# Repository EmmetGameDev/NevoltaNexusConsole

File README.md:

[See the build and design on YouTube!](https://www.youtube.com/watch?v=XNRuj0vmZO0)

# Nevolta Nexus

The Nexus is a **retro games console** based on the Raspberry Pi Zero 2W and the ESP32-S3. The console features:
- Custom wireless controller
- Active cooling system
- Custom PCBs
- Fully open source design

"Nevolta" is the name for my personal console line-up. **(more are coming soon!)**

# Files

- The "Printables" folder contains labeled 3D printable files for the Console unit as well as the Controller.
- The "PCBs" folder contains GERBER files, as well as KiCad project, schematic, and layout files.
- The "Firmware" folder contains two .INO files for the Console and Controller ESPs, respectively.

# Setup

## ESP32-S3 Microcontrollers
- The ESPs can be programmed when already soldered onto the board, since a data connection is present in the USB-C connector.
- Respective firmware (.INO) files are to be flashed via the [Arduino IDE](https://www.arduino.cc/en/software/)

## Raspberry Pi Zero 2W
- A generic RetroPie build is used for the Pi, which is included in the [Raspberry Pi Imager](https://www.raspberrypi.com/software/)
- Software [GPIOnext](https://github.com/mholgatem/GPIOnext) is used for GPIO button usage according to the instructions provided on the repo.
- [This tutorial](https://www.youtube.com/watch?v=BV_nVu8Be7M) is a good reference for the setup of the software.

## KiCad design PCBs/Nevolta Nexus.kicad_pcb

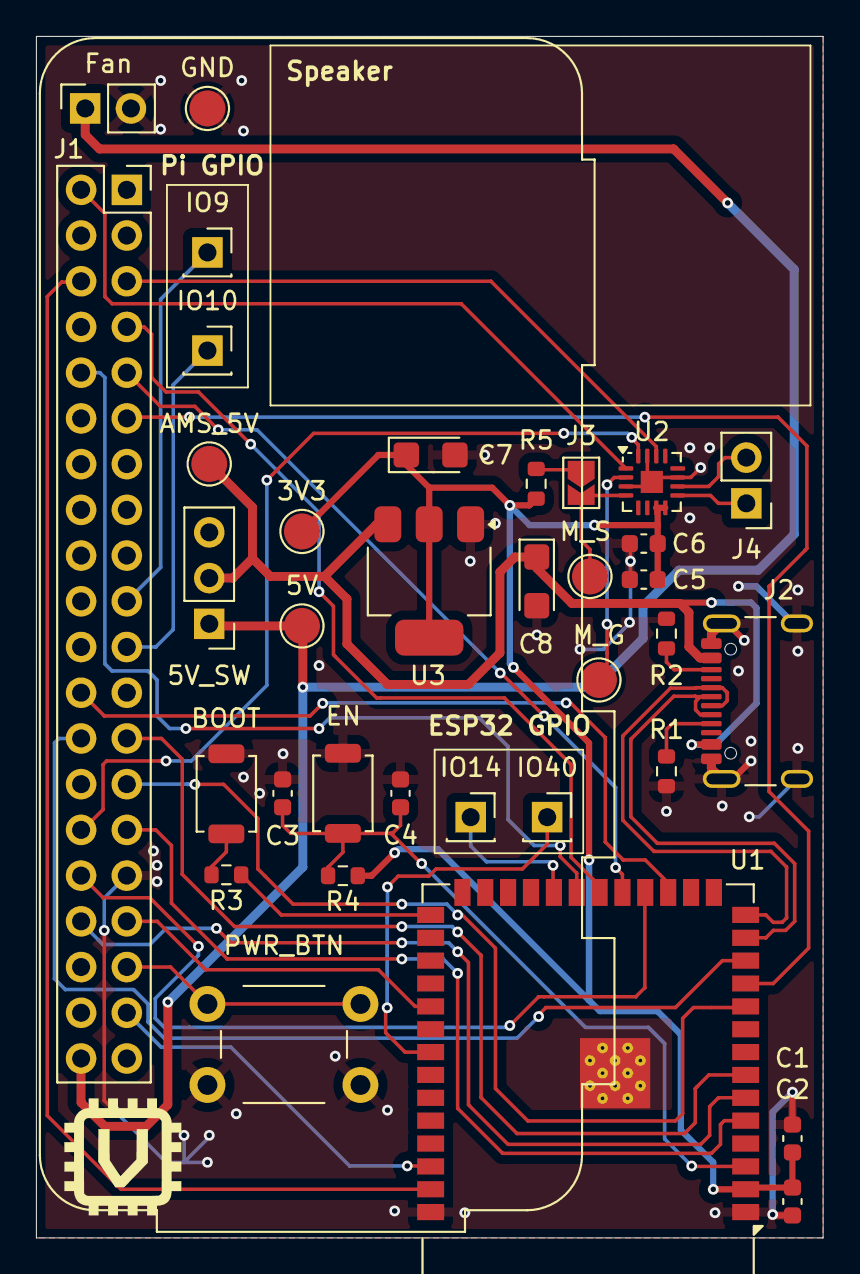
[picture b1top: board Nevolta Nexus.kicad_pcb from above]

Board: 2 copper layers, 43.7 x 66.8 mm, 35 parts (0 on the bottom side), 38 nets.

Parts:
3V3: 3v3; TestPoint_Pad_D2.0mm
5V: 5V; TestPoint_Pad_D2.0mm
5V_SW: Vbus_SW; PinHeader_1x03_P2.54mm_Vertical
AMS_5V: AMS_5V; TestPoint_Pad_D2.0mm
BOOT: BOOT; SW_SPST_TS-1088-xR020
C1: 22uF; C_0603_1608Metric
C2, C4, C6: 100nF; C_0603_1608Metric
C3, C5: 10uF; C_0603_1608Metric
C7: 22uF; CP_EIA-3216-18_Kemet-A
C8: 10uF; CP_EIA-3216-18_Kemet-A
EN: EN; SW_SPST_TS-1088-xR020
Fan: Fan_Conn; PinSocket_1x02_P2.54mm_Vertical
GND: GND; TestPoint_Pad_D2.0mm
IO9: Pi_IO9; PinSocket_1x01_P2.54mm_Vertical
IO10: Pi_IO10; PinSocket_1x01_P2.54mm_Vertical
IO14: GPIO14; PinSocket_1x01_P2.54mm_Vertical
IO40: GPIO40; PinSocket_1x01_P2.54mm_Vertical
J1: Pi Zero 2W; Raspberry Pi Zero 2 W - Clear
J2: USB_C_Receptacle_USB2.0_16P; USB_C_Receptacle_GCT_USB4105-xx-A_16P_TopMnt_Horizontal
J3: SolderJumper-2_P1.3mm_Open_TrianglePad1.0x1.5mm
J4: SpeakerConn; PinHeader_1x02_P2.54mm_Vertical
M_G: MAX_GAIN; TestPoint_Pad_D2.0mm
M_S: MAX_SD; TestPoint_Pad_D2.0mm
PWR_BTN: PWR; SW_PUSH_8mm_H5mm_custom
R1, R2: 5.1k; R_0603_1608Metric
R3: 100R; R_0603_1608Metric
R4: 10k; R_0603_1608Metric
R5: 1M; R_0603_1608Metric
U1: ESP32-S3-WROOM-1
U2: MAX98357A; TQFN-16-1EP_3x3mm_P0.5mm_EP1.23x1.23mm
U3: AMS1117-3.3; SOT-223-3_TabPin2

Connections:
+3V3: 3V3.1, C1.1, C2.1, C5.2, C6.2, C7.1, R4.1, R5.1, U1.2 (3V3), U2.7 (VDD), U2.8 (VDD), U3.2 (VO)
+5V: 5V.1, 5V_SW.1 (A), Fan.1, J1.40
AMS_5V: 5V_SW.2 (B), AMS_5V.1, C8.1, J2.A4 (VBUS), J2.A9 (VBUS), J2.B4 (VBUS), J2.B9 (VBUS), U3.3 (VI)
BOOT: R3.1, U1.27 (IO0)
BTN_A: J1.37, U1.38 (IO2)
BTN_B: J1.34, U1.6 (IO6)
BTN_DOWN: J1.9, U1.19 (IO11)
BTN_L: J1.32, U1.18 (IO10)
BTN_LEFT: J1.7, U1.20 (IO12)
BTN_R: J1.6, U1.39 (IO1)
BTN_RIGHT: J1.10, U1.21 (IO13)
BTN_SELECT: J1.25, U1.7 (IO7)
BTN_START: J1.27, U1.10 (IO17)
BTN_UP: J1.11, U1.11 (IO18)
BTN_VOLD: J1.26, U1.12 (IO8)
BTN_VOLU: J1.24, U1.17 (IO9)
BTN_X: J1.33, U1.31 (IO38)
BTN_Y: J1.29, U1.5 (IO5)
Data+: J2.A6 (D+), J2.B6 (D+), U1.14 (USB_D+)
Data-: J2.A7 (D-), J2.B7 (D-), U1.13 (USB_D-)
EN: C3.1, C4.1, EN.1, R4.2, U1.3 (EN)
GND: BOOT.2, C1.2, C2.2, C3.2, C4.2, C5.1, C6.1, C7.2, C8.2, EN.2, Fan.2, GND.1, J1.31, J2.A1 (GND), J2.A12 (GND), J2.B1 (GND), J2.B12 (GND), J2.S1 (SHIELD), PWR_BTN.2, R1.2, R2.1, U1.1 (GND), U1.40 (GND), U1.41 (GND), U2.3 (GND), U2.11 (GND), U2.15 (GND), U2.17 (PAD), U3.1 (GND)
GPIO14: IO14.1, U1.22 (IO14)
GPIO40: IO40.1, U1.33 (IO40)
I2S_BCLK: J1.30, U2.16 (BCLK)
I2S_DIN: J1.2, U2.1 (DIN)
I2S_LRC: J1.5, U2.14 (LRCLK)
MAX_GAIN: M_G.1, U2.2 (GAIN_SLOT)
MAX_SD: J3.2, M_S.1, U2.4 (~SD_MODE)
unnamed: J2.A5 (CC1), R1.1
unnamed: J2.B5 (CC2), R2.2
unnamed: J3.1, R5.2
unnamed: J4.1, U2.9 (OUTP)
unnamed: J4.2, U2.10 (OUTN)
unnamed: BOOT.1, R3.2
POWER_BTN: J1.35, PWR_BTN.1
Pi_GPIO9: IO9.1, J1.19
Pi_GPIO10: IO10.1, J1.21

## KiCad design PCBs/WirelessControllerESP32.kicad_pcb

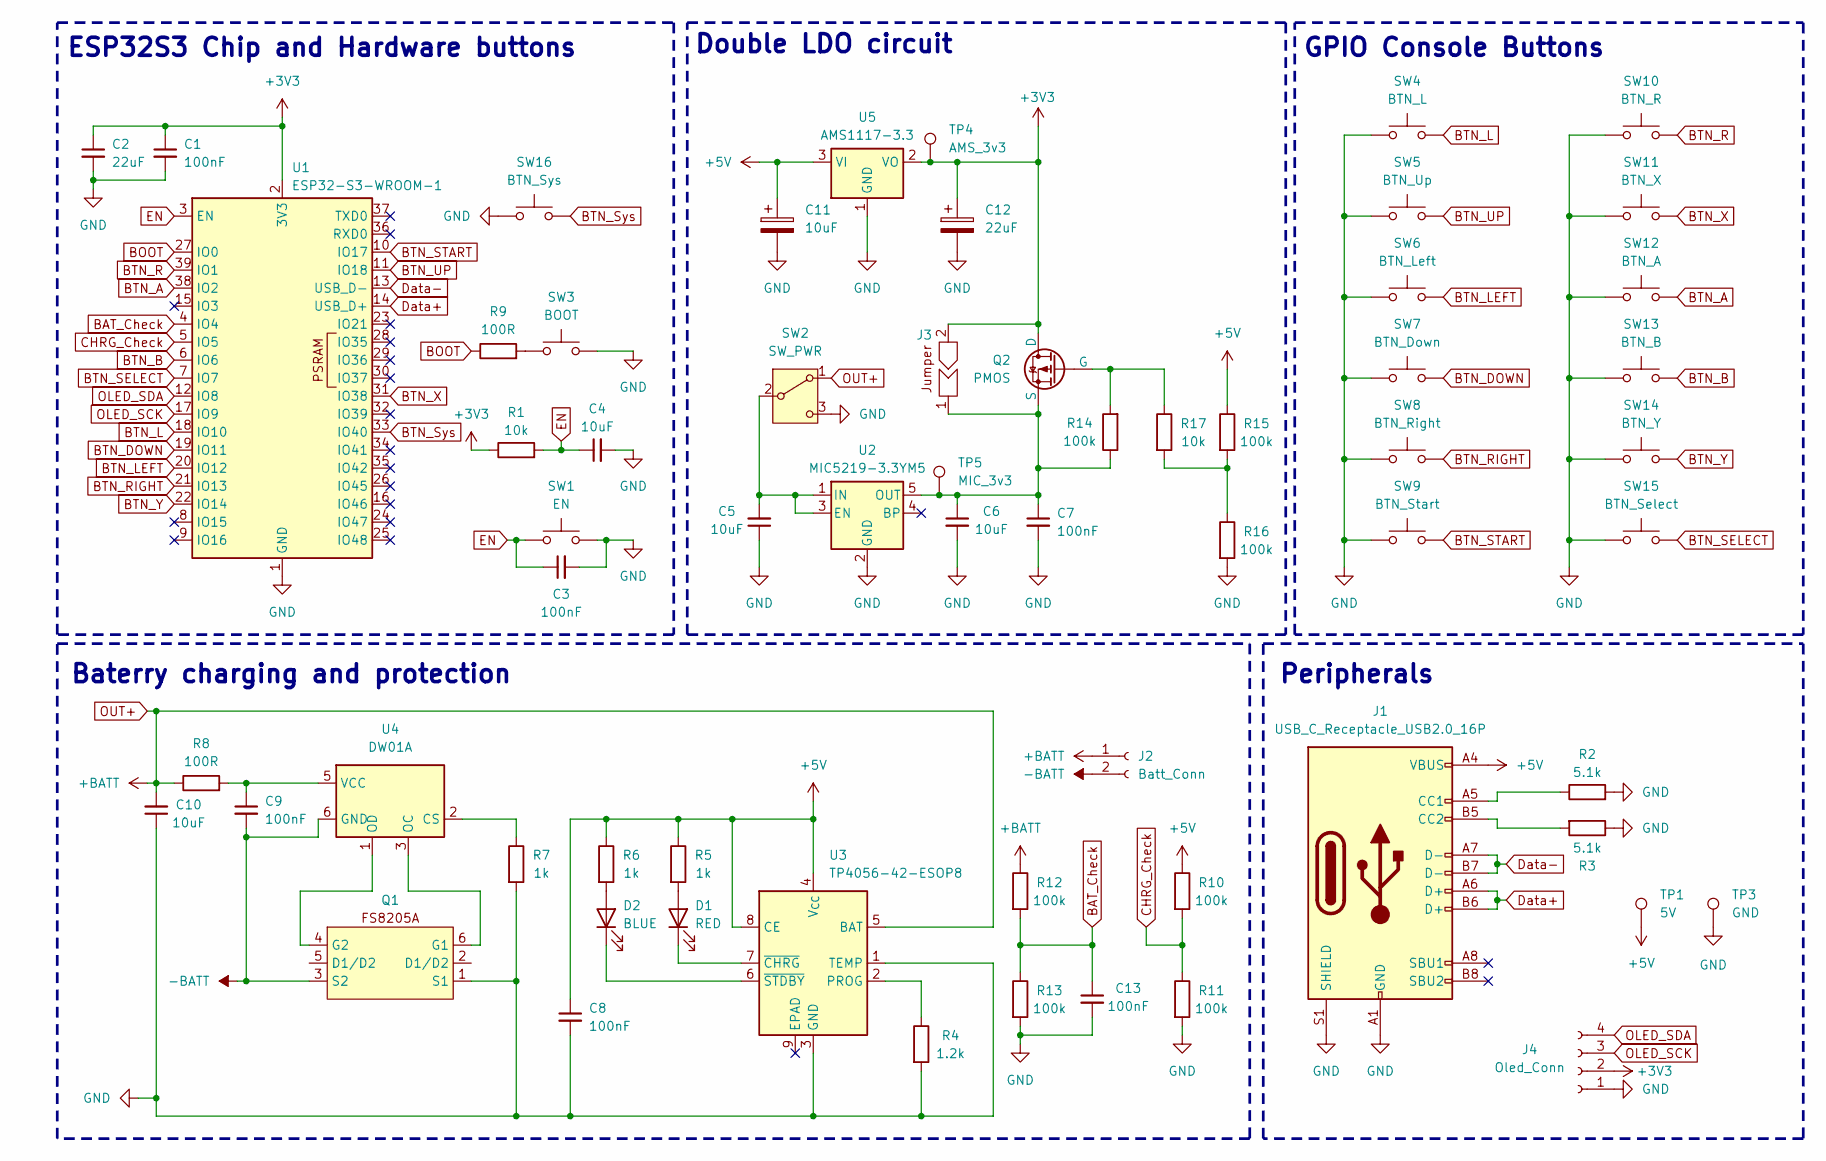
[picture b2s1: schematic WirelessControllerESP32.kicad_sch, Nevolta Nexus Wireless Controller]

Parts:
C1, C3, C7, C8, C9, C13: 100nF; C_0603_1608Metric
C2: 22uF; C_0603_1608Metric
C4, C5, C6, C10: 10uF; C_0603_1608Metric
C11: 10uF; CP_EIA-3216-18_Kemet-A
C12: 22uF; CP_EIA-3216-18_Kemet-A
D1: RED; LED_0603_1608Metric
D2: BLUE; LED_0603_1608Metric
J1: USB_C_Receptacle_USB2.0_16P; USB_C_Receptacle_GCT_USB4105-xx-A_16P_TopMnt_Horizontal
J2: Batt_Conn; JST_ZH_S2B-ZR-SM4A-TF_1x02-1MP_P1.50mm_Horizontal
J3: R_0603_1608Metric
J4: Oled_Conn; OLED128x32_1x04_P2.54mm_socket
Q1: SOT-23-6L_TCP
Q2: PMOS; SOT-23
R1, R17: 10k; R_0603_1608Metric
R2, R3: 5.1k; R_0603_1608Metric
R4: 1.2k; R_0603_1608Metric
R5, R6, R7: 1k; R_0603_1608Metric
R8, R9: 100R; R_0603_1608Metric
R10, R11, R12, R13, R14, R15, R16: 100k; R_0603_1608Metric
SW1: EN; SW_SPST_TS-1088-xR020
SW2: SW_PWR; PinSocket_1x03_P2.54mm_Vertical
SW3: BOOT; SW_SPST_TS-1088-xR020
SW4: BTN_L; TS-1224VW
SW5: BTN_Up; SW_PUSH_8mm_H5mm_custom
SW6: BTN_Left; SW_PUSH_8mm_H5mm_custom
SW7: BTN_Down; SW_PUSH_8mm_H5mm_custom
SW8: BTN_Right; SW_PUSH_8mm_H5mm_custom
SW9: BTN_Start; SW_PUSH_8mm_H5mm_custom
SW10: BTN_R; TS-1224VW
SW11: BTN_X; SW_PUSH_8mm_H5mm_custom
SW12: BTN_A; SW_PUSH_8mm_H5mm_custom
SW13: BTN_B; SW_PUSH_8mm_H5mm_custom
SW14: BTN_Y; SW_PUSH_8mm_H5mm_custom
SW15: BTN_Select; SW_PUSH_8mm_H5mm_custom
SW16: BTN_Sys; SW_PUSH_8mm_H5mm_custom
TP1: 5V; TestPoint_Pad_D2.0mm
TP3: GND; TestPoint_Pad_D2.0mm
TP4: AMS_3v3; TestPoint_Pad_D2.0mm
TP5: MIC_3v3; TestPoint_Pad_D2.0mm
U1: ESP32-S3-WROOM-1
U2: MIC5219-3.3YM5; SOT-23-5
U3: TP4056-42-ESOP8; SOIC-8-1EP_3.9x4.9mm_P1.27mm_EP2.41x3.3mm_ThermalVias
U4: DW01A; SOT-23-6
U5: AMS1117-3.3; SOT-223-3_TabPin2

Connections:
+3V3: C1.1, C2.1, C12.1, J3.2, J4.2, Q2.1 (D), R1.1, TP4.1, U1.2 (3V3), U5.2 (VO)
+5V: C8.1, C11.1, J1.A4 (VBUS), J1.A9 (VBUS), J1.B4 (VBUS), J1.B9 (VBUS), R5.1, R6.1, R10.1, R15.1, TP1.1, U3.4 (V_{CC}), U3.8 (CE), U5.3 (VI)
-BATT: C9.2, J2.2, Q1.3 (S2), U4.6 (GND)
BAT_Check: C13.1, R12.2, R13.1, U1.4 (IO4)
BOOT: R9.1, U1.27 (IO0)
BTN_A: SW12.2, U1.38 (IO2)
BTN_B: SW13.2, U1.6 (IO6)
BTN_DOWN: SW7.2, U1.19 (IO11)
BTN_L: SW4.2, U1.18 (IO10)
BTN_LEFT: SW6.2, U1.20 (IO12)
BTN_R: SW10.2, U1.39 (IO1)
BTN_RIGHT: SW8.2, U1.21 (IO13)
BTN_SELECT: SW15.2, U1.7 (IO7)
BTN_START: SW9.2, U1.10 (IO17)
BTN_Sys: SW16.2, U1.33 (IO40)
BTN_UP: SW5.2, U1.11 (IO18)
BTN_X: SW11.2, U1.31 (IO38)
BTN_Y: SW14.2, U1.22 (IO14)
CHRG_Check: R10.2, R11.1, U1.5 (IO5)
Data+: J1.A6 (D+), J1.B6 (D+), U1.14 (USB_D+)
Data-: J1.A7 (D-), J1.B7 (D-), U1.13 (USB_D-)
EN: C3.1, C4.1, R1.2, SW1.1, U1.3 (EN)
GND: C1.2, C2.2, C3.2, C4.2, C5.1, C6.2, C7.2, C8.2, C10.1, C11.2, C12.2, C13.2, J1.A1 (GND), J1.A12 (GND), J1.B1 (GND), J1.B12 (GND), J1.S1 (SHIELD), J4.1, Q1.1 (S1), R2.2, R3.1, R4.2, R7.2, R11.2, R13.2, R16.2, SW1.2, SW2.3 (C), SW3.2, SW4.1, SW5.1, SW6.1, SW7.1, SW8.1, SW9.1, SW10.1, SW11.1, SW12.1, SW13.1, SW14.1, SW15.1, SW16.1, TP3.1, U1.1 (GND), U1.40 (GND), U1.41 (GND), U2.2 (GND), U3.1 (TEMP), U3.3 (GND), U5.1 (GND)
unnamed: D1.2 (A), R5.2
unnamed: D1.1 (K), U3.7 (~CHRG)
unnamed: D2.2 (A), R6.2
unnamed: D2.1 (K), U3.6 (~STDBY)
unnamed: J1.A5 (CC1), R2.1
unnamed: J1.B5 (CC2), R3.2
unnamed: Q1.6 (G1), U4.3 (OC)
unnamed: Q1.4 (G2), U4.1 (OD)
unnamed: Q2.2 (G), R14.2, R17.1
unnamed: C6.1, C7.1, J3.1, Q2.3 (S), R14.1, TP5.1, U2.5 (OUT)
unnamed: R9.2, SW3.1
unnamed: R15.2, R16.1, R17.2
unnamed: C5.2, SW2.2 (B), U2.1 (IN), U2.3 (EN)
unnamed: R4.1, U3.2 (PROG)
unnamed: R7.1, U4.2 (CS)
unnamed: C9.1, R8.2, U4.5 (VCC)
OLED_SCK: J4.3, U1.17 (IO9)
OLED_SDA: J4.4, U1.12 (IO8)
OUT+: C10.2, J2.1, R8.1, R12.1, SW2.1 (A), U3.5 (BAT)

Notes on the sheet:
Peripherals
ESP32S3 Chip and Hardware buttons
GPIO Console Buttons
Double LDO circuit
Baterry charging and protection

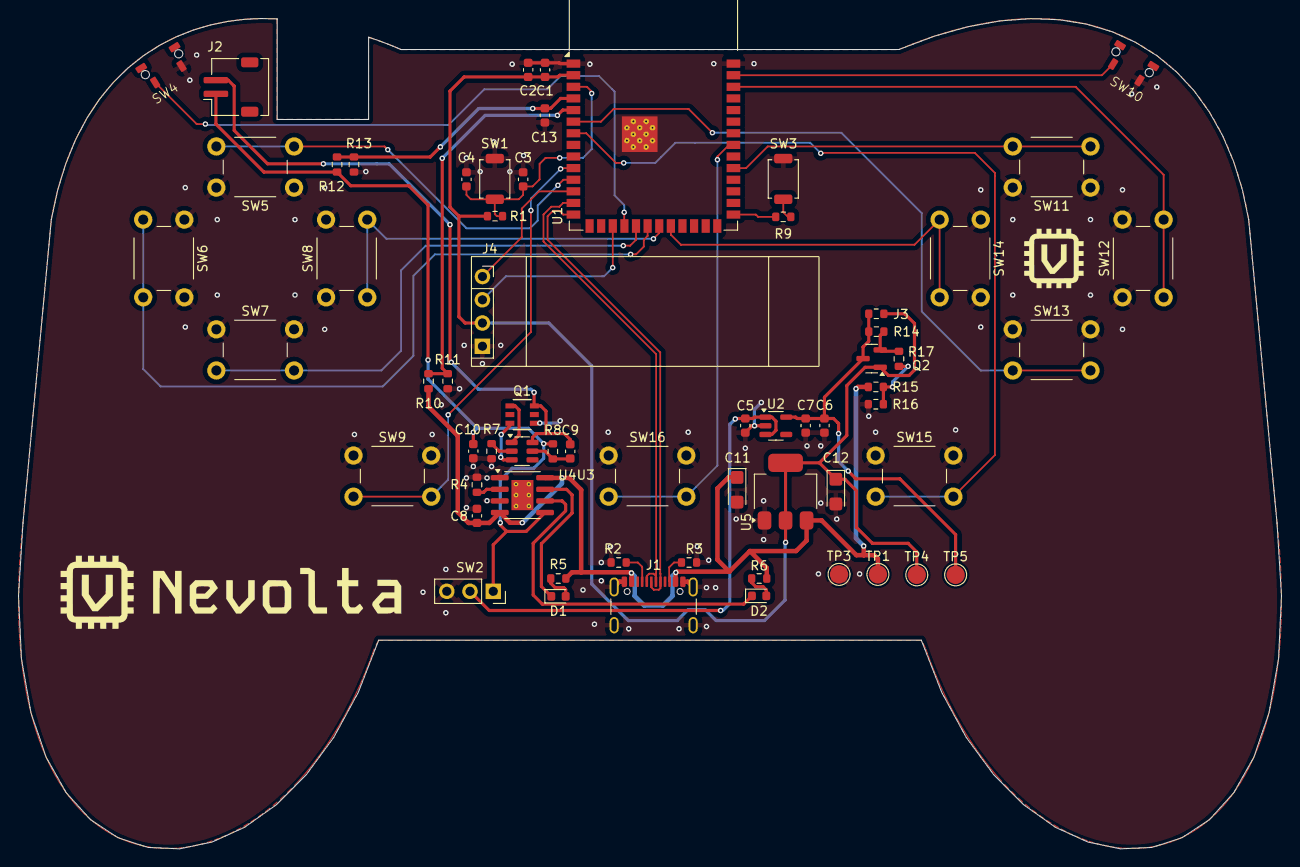
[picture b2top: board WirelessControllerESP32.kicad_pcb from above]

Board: 2 copper layers, 138.1 x 90.8 mm, 63 parts (0 on the bottom side), 42 nets.

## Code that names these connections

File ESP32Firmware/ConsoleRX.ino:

#include <esp_now.h>
#include <WiFi.h>
#include <esp_wifi.h>

typedef struct struct_message {
  char a[32];
  int b;
  float c;
  bool d;
} struct_message;
struct_message myData;

int btn_L_Pin = 10;
int btn_Up_Pin = 18;
int btn_Right_Pin = 13;
int btn_Down_Pin = 11;
int btn_Left_Pin = 12;
int btn_Start_Pin = 17;
int btn_Select_Pin = 7;
int btn_X_Pin = 38;
int btn_A_Pin = 2;
int btn_B_Pin = 6;
int btn_Y_Pin = 5;
int btn_R_Pin = 1;

int btn_VolD_Pin = 8;
int btn_VolU_Pin = 9;


void OnDataRecv(const uint8_t * mac, const uint8_t *incomingData, int len) {
  memcpy(&myData, incomingData, sizeof(myData));
  /*Serial.print("Bytes received: ");
  Serial.println(len);
  Serial.print("Int: ");
  Serial.println(myData.b);
  Serial.print("Bool: ");
  Serial.println(myData.d);
  Serial.println();*/
  buttonPressed(myData.b, myData.d);
}

void readMacAddress(){
  uint8_t baseMac[6];
  esp_err_t ret = esp_wifi_get_mac(WIFI_IF_STA, baseMac);
  if (ret == ESP_OK) {
    Serial.printf("%02x:%02x:%02x:%02x:%02x:%02x\n",
                  baseMac[0], baseMac[1], baseMac[2],
                  baseMac[3], baseMac[4], baseMac[5]);
  } else {
    Serial.println("Failed to read MAC address");
  }
}

void buttonPressed(int buttonID, bool doIPress){
  uint8_t pressAction;
  if(doIPress == true){
    Serial.print("Button pressed: ");
    pressAction = LOW;
  }else{
    Serial.print("Button unpressed: ");
    pressAction = HIGH;
  }
  switch (buttonID) {
    case 0:
      digitalWrite(btn_L_Pin, pressAction);
      break;
    case 1:
      digitalWrite(btn_Up_Pin, pressAction);
      break;
    case 2:
      digitalWrite(btn_Right_Pin, pressAction);
      break;
    case 3:
      digitalWrite(btn_Down_Pin, pressAction);
      break;
    case 4:
      digitalWrite(btn_Left_Pin, pressAction);
      break;
    case 5:
      digitalWrite(btn_Start_Pin, pressAction);
      break;
    case 6:
      digitalWrite(btn_Select_Pin, pressAction);
      break;
    case 7:
      digitalWrite(btn_X_Pin, pressAction);
      break;
    case 8:
      digitalWrite(btn_A_Pin, pressAction);
      break;
    case 9:
      digitalWrite(btn_B_Pin, pressAction);
      break;
    case 10:
      digitalWrite(btn_Y_Pin, pressAction);
      break;
    case 11:
      digitalWrite(btn_R_Pin, pressAction);
      break;
    case 15:
      digitalWrite(btn_VolD_Pin, pressAction);
      break;
    case 16:
      digitalWrite(btn_VolU_Pin, pressAction);
      break;
    default:
      break;
  }
  Serial.print("\n");
}

void setup(){
  Serial.begin(115200);

  WiFi.mode(WIFI_STA);
  WiFi.disconnect();

  Serial.println(WiFi.macAddress());

  if (esp_now_init() != ESP_OK){
    Serial.println("RX ESPNOW FAIL");
    return;
  }

  esp_now_register_recv_cb(OnDataRecv);

  Serial.println("RX READY");
  digitalWrite(btn_L_Pin, HIGH);
  pinMode(btn_L_Pin, OUTPUT);

  digitalWrite(btn_Up_Pin, HIGH);
  pinMode(btn_Up_Pin, OUTPUT);

  digitalWrite(btn_Right_Pin, HIGH);
  pinMode(btn_Right_Pin, OUTPUT);

  digitalWrite(btn_Down_Pin, HIGH);
  pinMode(btn_Down_Pin, OUTPUT);

  digitalWrite(btn_Left_Pin, HIGH);
  pinMode(btn_Left_Pin, OUTPUT);

  digitalWrite(btn_Start_Pin, HIGH);
  pinMode(btn_Start_Pin, OUTPUT);

  digitalWrite(btn_Select_Pin, HIGH);
  pinMode(btn_Select_Pin, OUTPUT);

  digitalWrite(btn_X_Pin, HIGH);
  pinMode(btn_X_Pin, OUTPUT);

  digitalWrite(btn_A_Pin, HIGH);
  pinMode(btn_A_Pin, OUTPUT);

  digitalWrite(btn_B_Pin, HIGH);
  pinMode(btn_B_Pin, OUTPUT);

  digitalWrite(btn_Y_Pin, HIGH);
  pinMode(btn_Y_Pin, OUTPUT);

  digitalWrite(btn_R_Pin, HIGH);
  pinMode(btn_R_Pin, OUTPUT);

  digitalWrite(btn_VolD_Pin, HIGH);
  pinMode(btn_VolD_Pin, OUTPUT);
  
  digitalWrite(btn_VolU_Pin, HIGH);
  pinMode(btn_VolU_Pin, OUTPUT);

  Serial.println("Buttons READY");
}

void loop(){

}

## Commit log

2026-06-07 PCB files and Printables Added
2026-06-08 ESP32 firmware added
2026-06-08 Readme polish
